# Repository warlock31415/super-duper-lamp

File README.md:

# super-duper-lamp
This repo contains files for building a single direction traffic control unit using discrete logic. 

The circuit uses a 555 timer to generate a 1Hz signal which increments a BCD counter. The outputs from the counter are fed into logic gates
to ensure that the correct light is turned on. The green and red lights1 thus turn on for 6 seconds individually. And the yellow light turns 
on for 4 seconds.

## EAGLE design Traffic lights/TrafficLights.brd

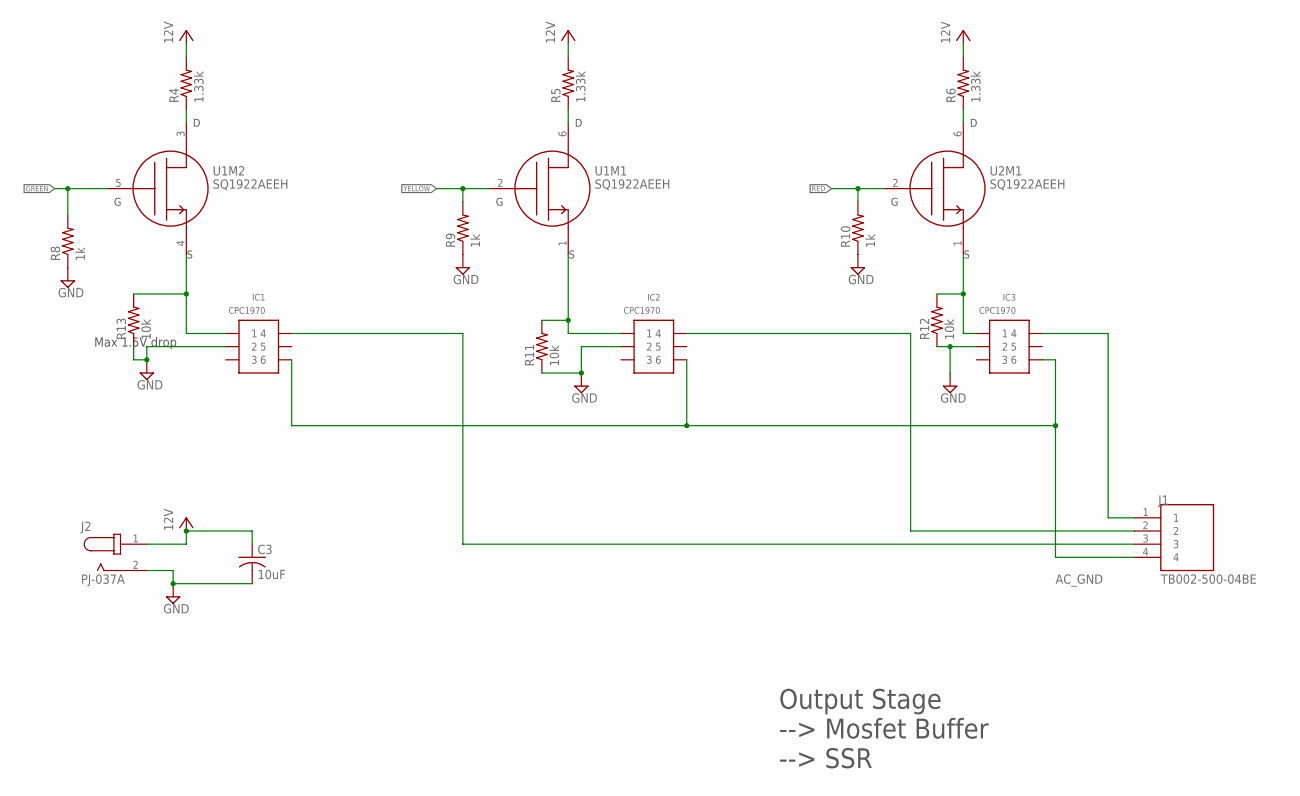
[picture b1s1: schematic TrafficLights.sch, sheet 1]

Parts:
C3: 10uF; C1206
IC1, IC2, IC3: CPC1970; 6-DIP
J1: TB002-500-04BE; CUI_TB002-500-04BE
J2: PJ-037A; CUI_PJ-037A
R4, R5, R6: 1.33k; R1206
R8, R9, R10: 1k; R1206
R11, R12: 10k; 0207/2V
R13: 10k; R1206
U1, U2: SQ1922AEEH; SOT-363

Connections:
AC_GND: IC1.P$6 (6), IC2.P$6 (6), IC3.P$6 (6), J1.4
GND: C3.2, IC1.P$2 (2), IC2.P$2 (2), IC3.P$2 (2), J2.2, R8.1, R9.1, R10.1, R11.1, R12.1, R13.1; also elsewhere on the board
GREEN: R8.2, U1.5 (G); also elsewhere on the board
unnamed: IC1.P$1 (1), R13.2, U1.4 (S)
unnamed: IC2.P$1 (1), R11.2, U1.1 (S)
unnamed: IC3.P$1 (1), R12.2, U2.1 (S)
unnamed: R4.1, U1.3 (D)
unnamed: R5.1, U1.6 (D)
unnamed: R6.1, U2.6 (D)
unnamed: IC2.P$4 (4), J1.2
unnamed: IC3.P$4 (4), J1.1
RED: R10.2, U2.2 (G); also elsewhere on the board
VAC: IC1.P$4 (4), J1.3
VCC: C3.1, J2.1, R4.2, R5.2, R6.2; also elsewhere on the board
YELLOW: R9.2, U1.2 (G); also elsewhere on the board

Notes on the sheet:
Max 1.5V drop
Output Stage --> Mosfet Buffer --> SSR

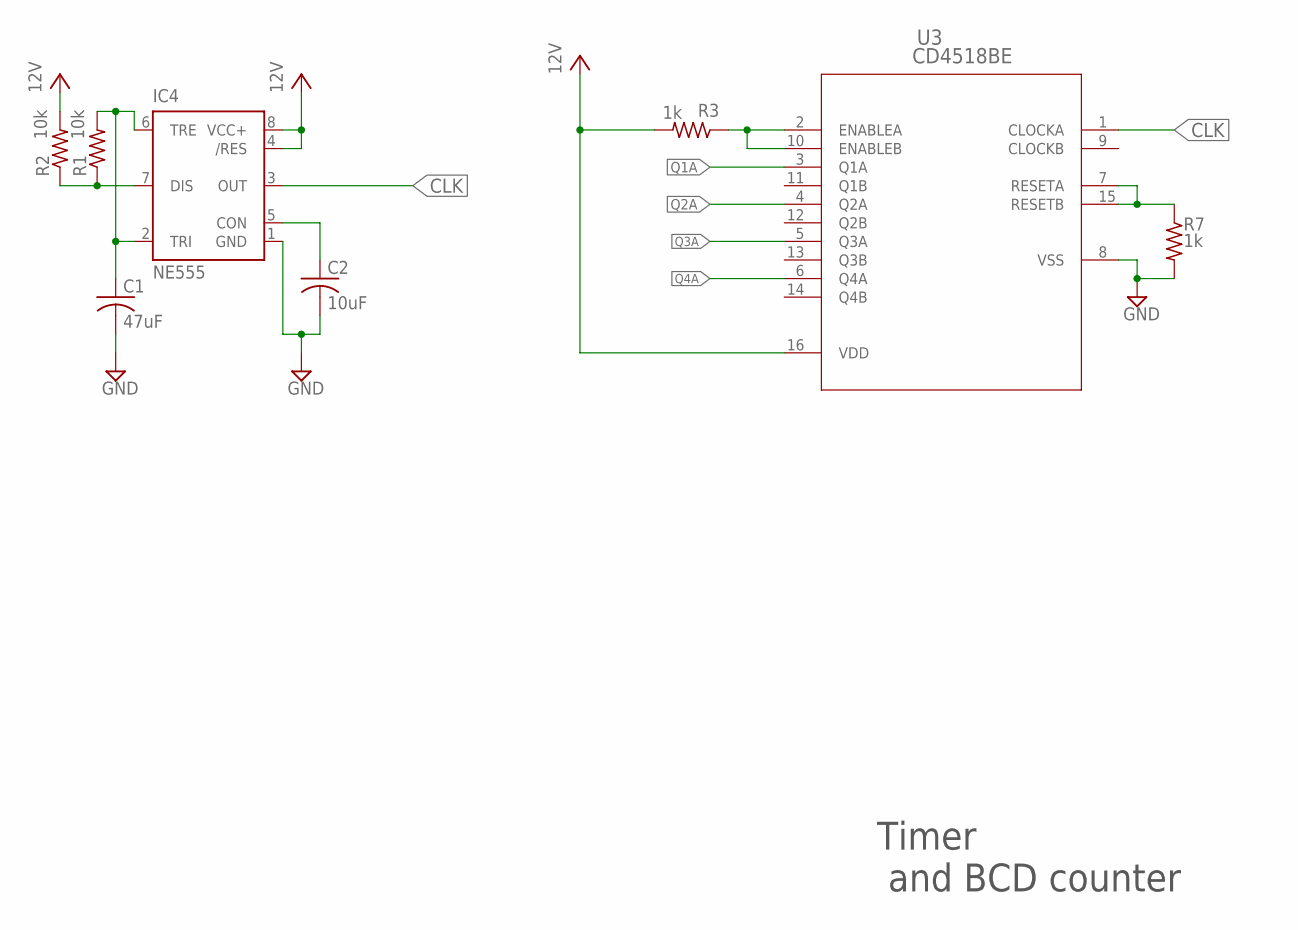
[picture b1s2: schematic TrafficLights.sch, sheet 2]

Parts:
C1: 47uF; C1206
C2: 10uF; C1206
IC4: NE555; DIL-08
R1, R2: 10k; R1206
R3, R7: 1k; R1206
U3: CD4518BE; N16

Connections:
CLK: IC4.3 (OUT), U3.1 (CLOCKA)
GND: C1.2, C2.2, IC4.1 (GND), R7.2, U3.8 (VSS); also elsewhere on the board
unnamed: IC4.7 (DIS), R1.1, R2.1
unnamed: C1.1, IC4.2 (TRI), IC4.6 (TRE), R1.2
unnamed: C2.1, IC4.5 (CON)
unnamed: R3.1, U3.2 (ENABLEA), U3.10 (ENABLEB)
unnamed: R7.1, U3.7 (RESETA), U3.15 (RESETB)
Q1A: U3.3 (Q1A)
Q2A: U3.4 (Q2A); also elsewhere on the board
Q3A: U3.5 (Q3A); also elsewhere on the board
Q4A: U3.6 (Q4A); also elsewhere on the board
VCC: IC4.4 (/RES), IC4.8 (VCC+), R2.2, R3.2, U3.16 (VDD); also elsewhere on the board

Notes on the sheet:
Timer and BCD counter

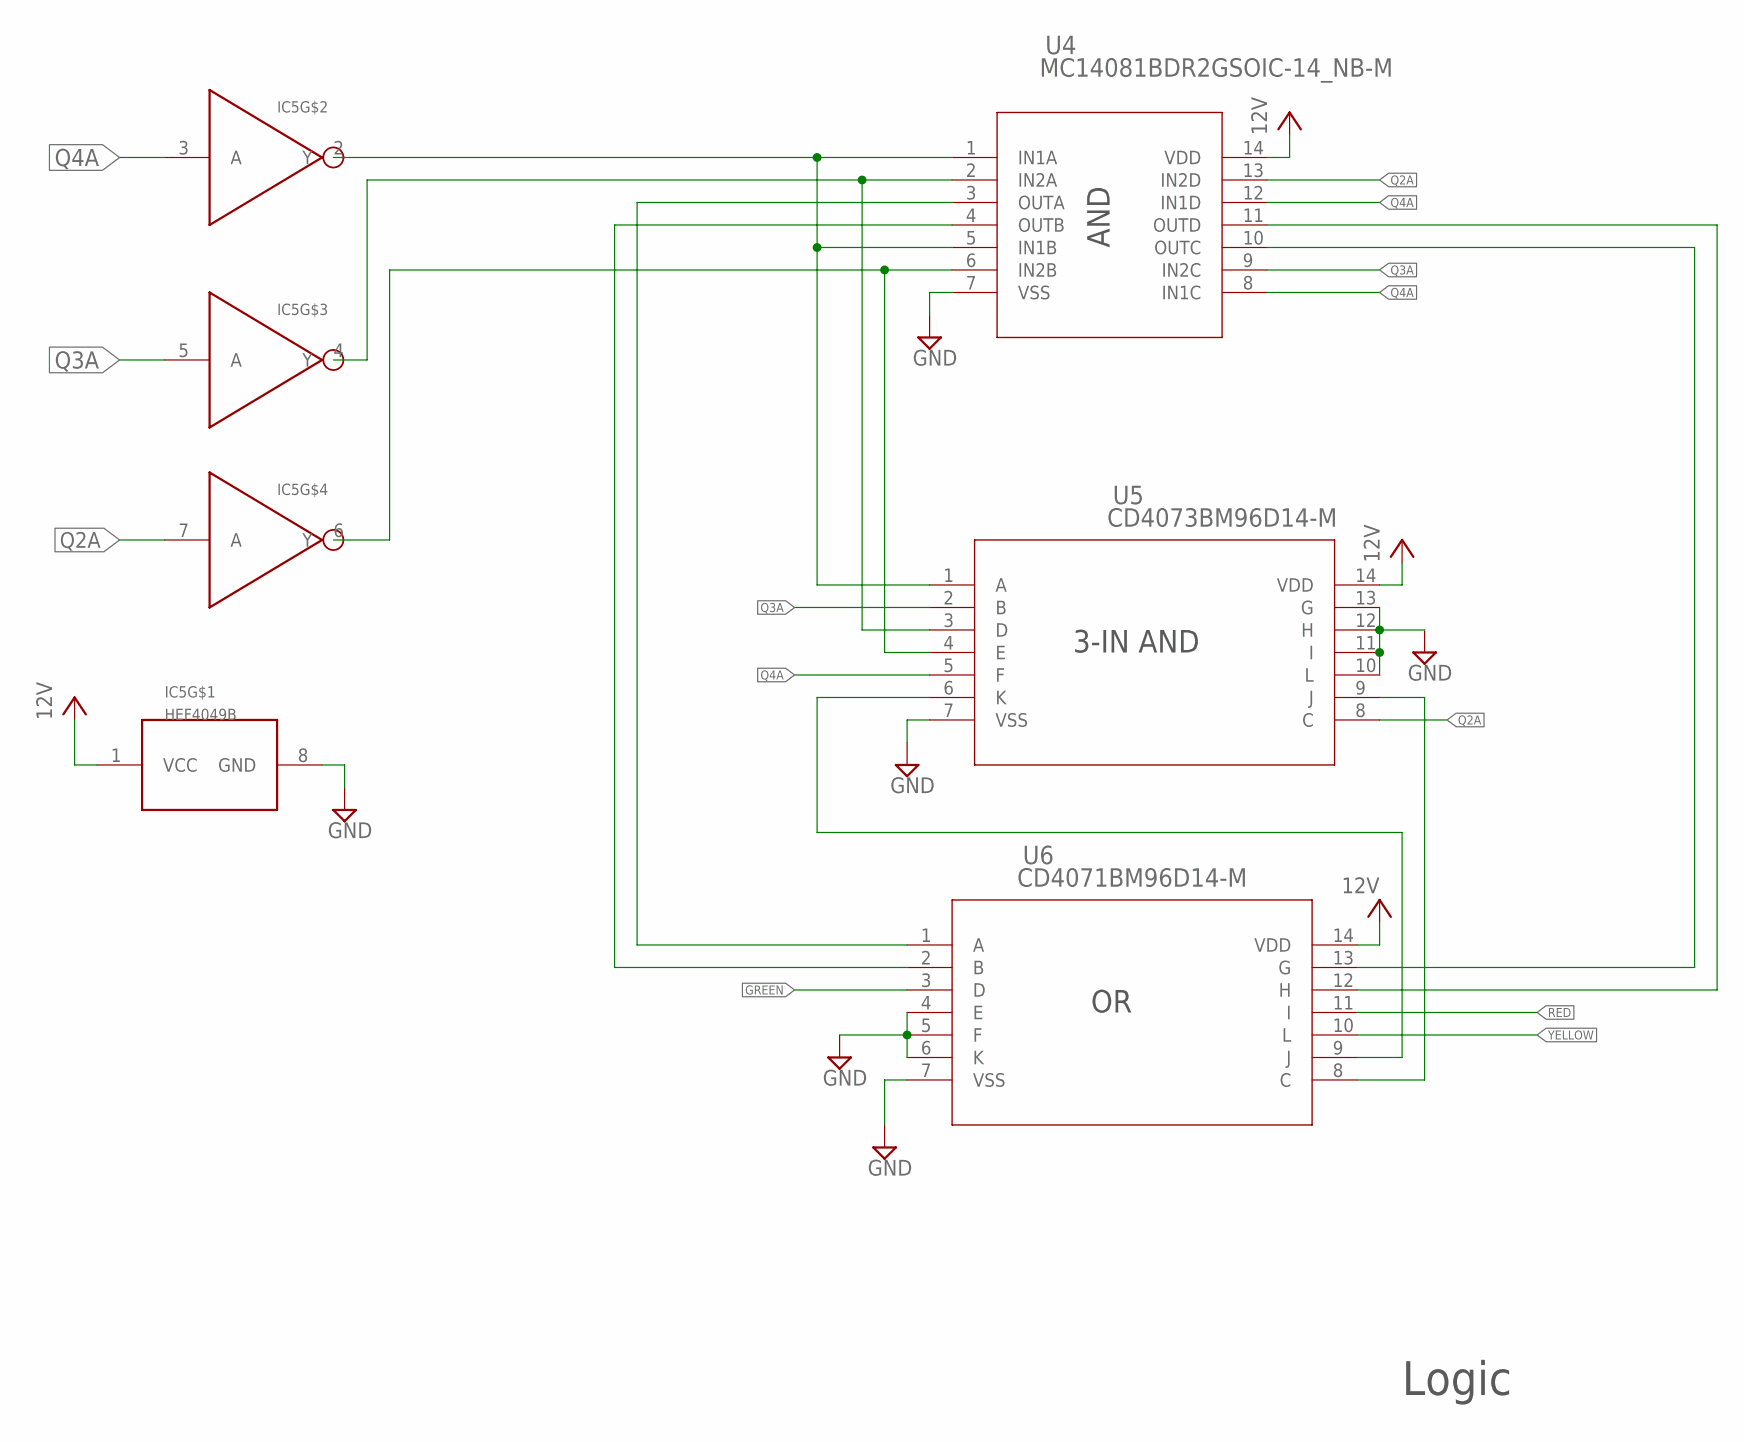
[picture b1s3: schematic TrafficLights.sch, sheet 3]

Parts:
IC5: HEF4049B; SO16
U4: MC14081BDR2GSOIC-14_NB-M; SOIC-14_NB-M
U5: CD4073BM96D14-M; D14-M
U6: CD4071BM96D14-M; D14-M

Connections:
GND: IC5.8 (GND), U4.7 (VSS), U5.7 (VSS), U5.10 (L), U5.11 (I), U5.12 (H), U5.13 (G), U6.4 (E), U6.5 (F), U6.6 (K), U6.7 (VSS); also elsewhere on the board
GREEN: U6.3 (D); also elsewhere on the board
unnamed: IC5.2 (Y), U4.1 (IN1A), U4.5 (IN1B), U5.1 (A)
unnamed: IC5.4 (Y), U4.2 (IN2A), U5.3 (D)
unnamed: IC5.6 (Y), U4.6 (IN2B), U5.4 (E)
unnamed: U4.3 (OUTA), U6.1 (A)
unnamed: U4.4 (OUTB), U6.2 (B)
unnamed: U4.10 (OUTC), U6.13 (G)
unnamed: U4.11 (OUTD), U6.12 (H)
unnamed: U5.9 (J), U6.8 (C)
unnamed: U5.6 (K), U6.9 (J)
Q2A: IC5.7 (A), U4.13 (IN2D), U5.8 (C); also elsewhere on the board
Q3A: IC5.5 (A), U4.9 (IN2C), U5.2 (B); also elsewhere on the board
Q4A: IC5.3 (A), U4.8 (IN1C), U4.12 (IN1D), U5.5 (F); also elsewhere on the board
RED: U6.11 (I); also elsewhere on the board
VCC: IC5.1 (VCC), U4.14 (VDD), U5.14 (VDD), U6.14 (VDD); also elsewhere on the board
YELLOW: U6.10 (L); also elsewhere on the board

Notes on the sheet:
Logic
AND
3-IN AND

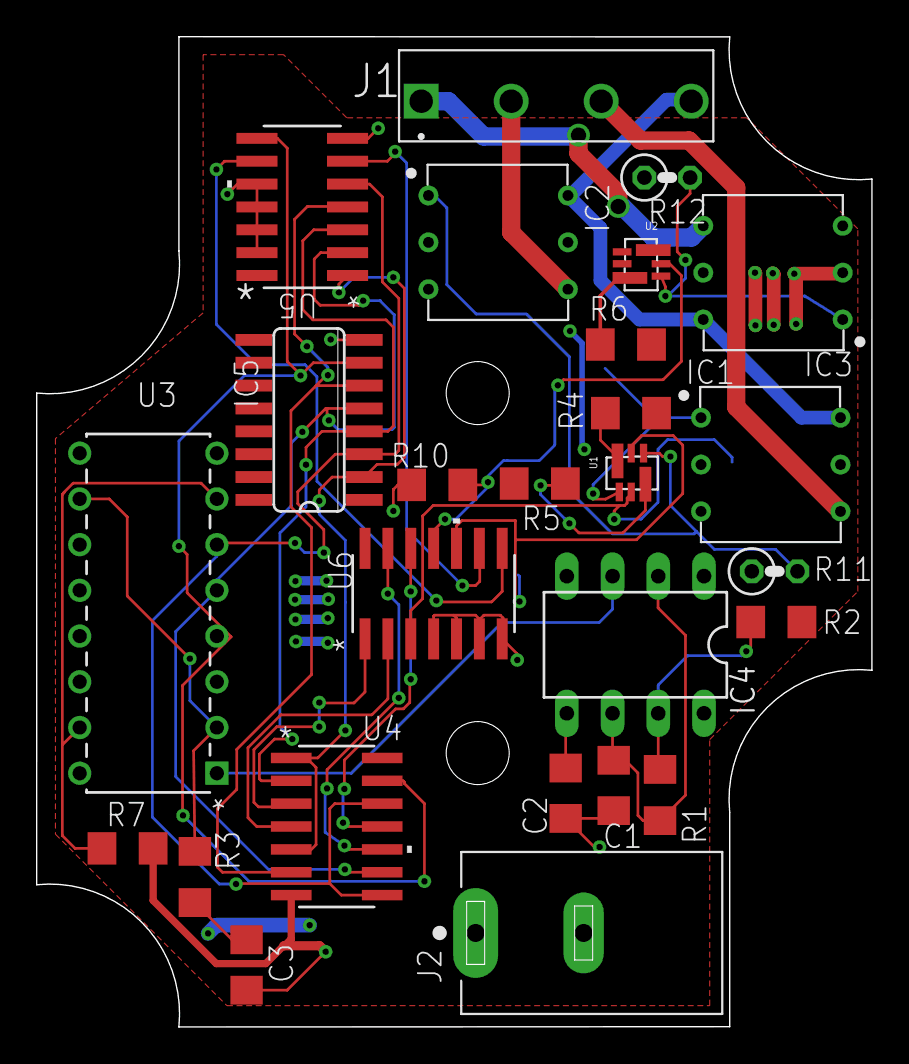
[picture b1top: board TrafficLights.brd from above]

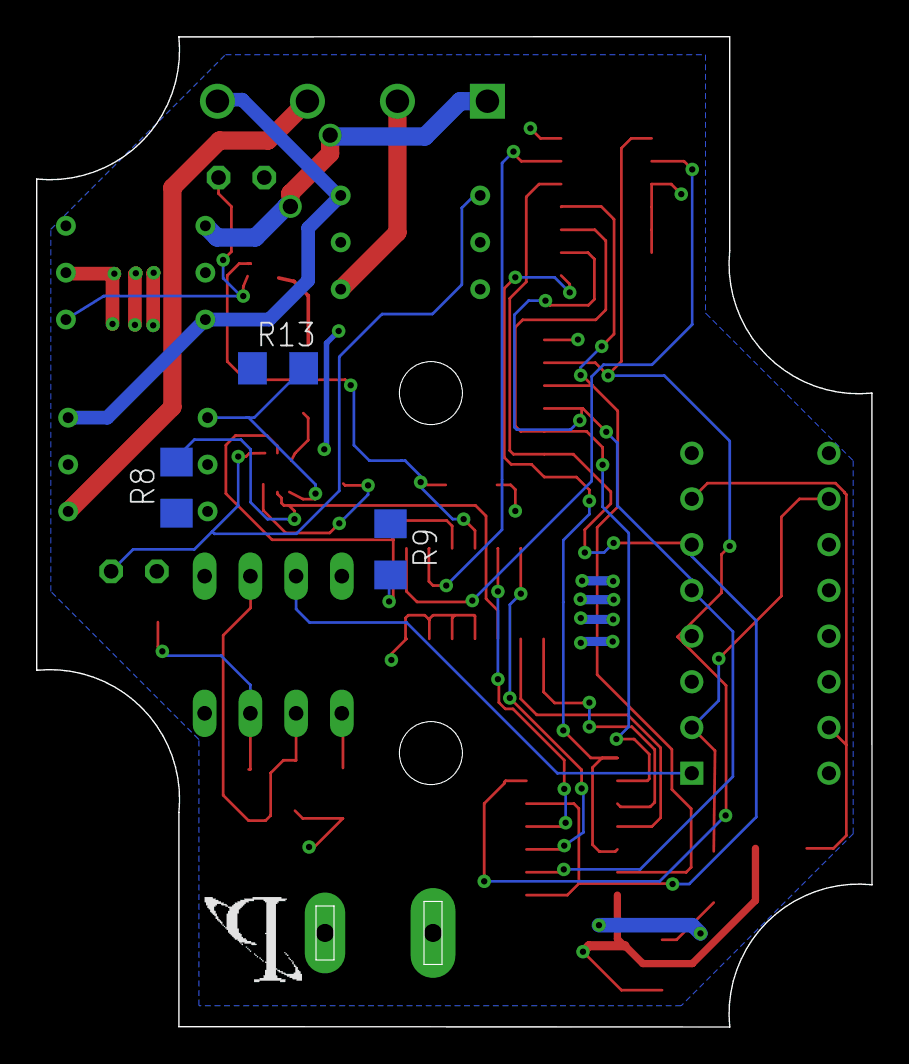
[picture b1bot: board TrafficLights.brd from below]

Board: 2 copper layers, 46.4 x 55.0 mm, 29 parts (3 on the bottom side), 33 nets.

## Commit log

2019-08-04 Readded files to repect .gitignore
2019-08-24 Added pull down resistors on SSRs, fixed inverter footprint.
2019-09-11 Fixed stuff
